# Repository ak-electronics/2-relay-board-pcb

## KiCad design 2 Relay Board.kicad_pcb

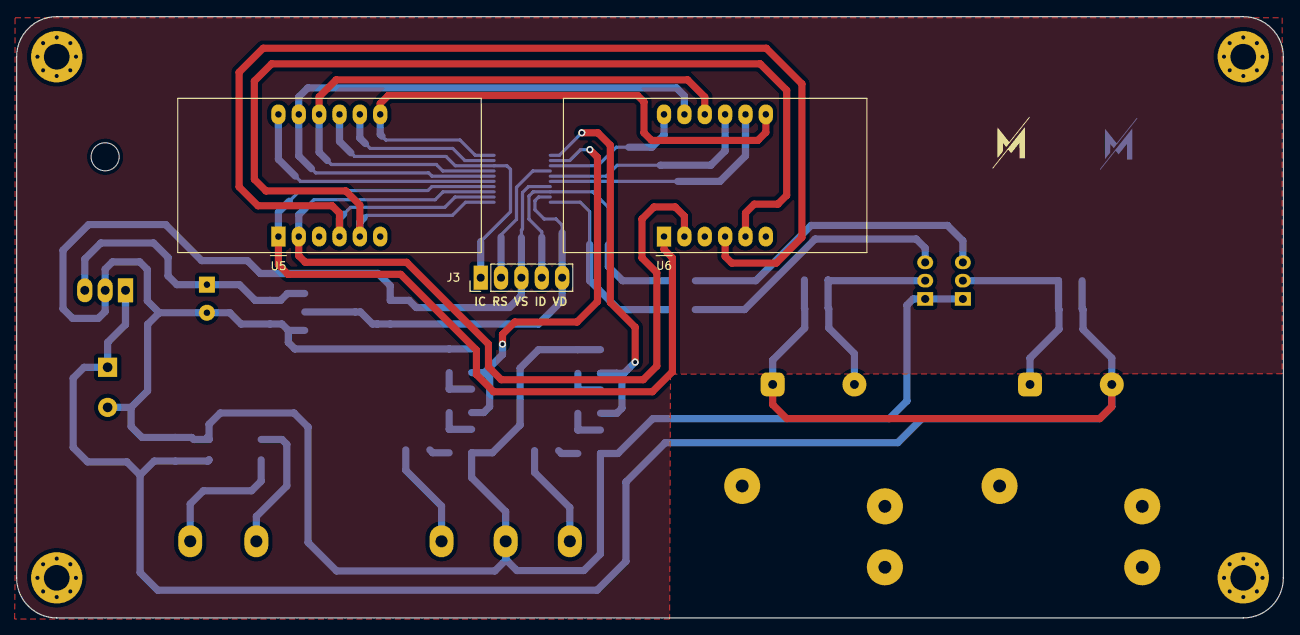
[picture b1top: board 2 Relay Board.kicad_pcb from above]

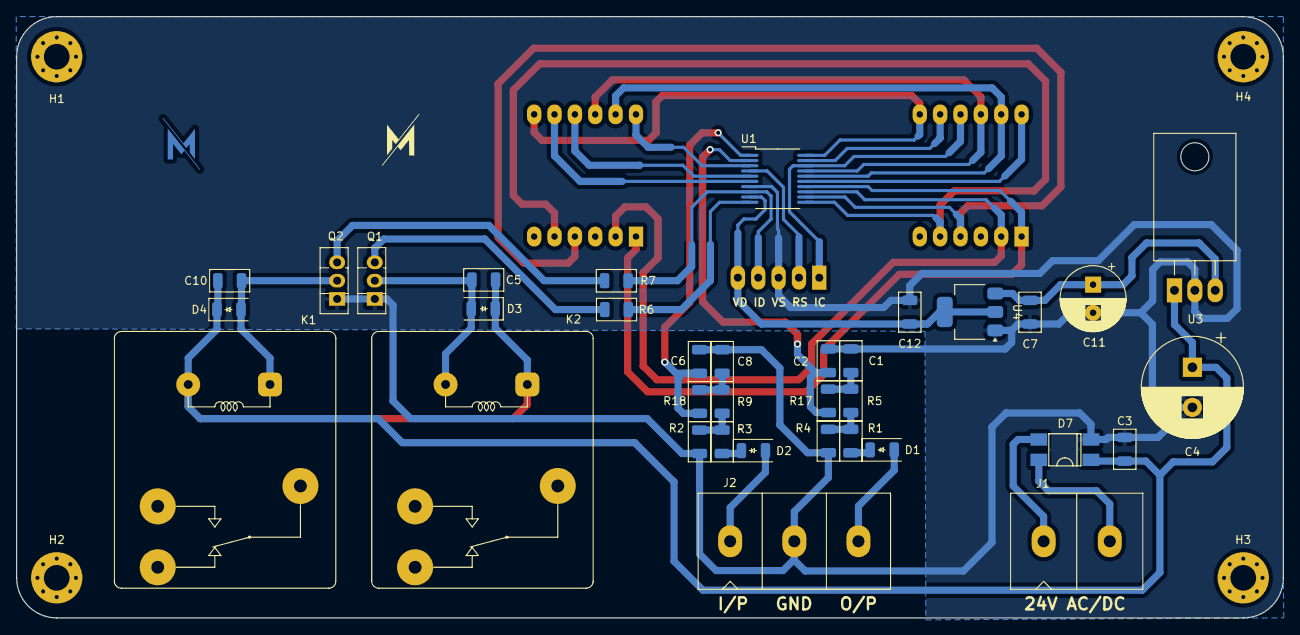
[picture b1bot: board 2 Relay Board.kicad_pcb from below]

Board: 2 copper layers, 158.0 x 75.0 mm, 42 parts (39 on the bottom side), 36 nets.

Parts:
C1, C2, C6, C8, C12: 10uf/50v; C_1206_3216Metric
C3, C5, C7, C10: 0.1uf/50v; C_1206_3216Metric
C4: 1000uf/50v; CP_Radial_D12.5mm_P5.00mm
C11: 470uf/25v; CP_Radial_D8.0mm_P3.50mm
D1, D2, D3, D4: D; D_1206
D7: D_Bridge_+-AA; MB10_bridge
H1, H2, H3, H4: MountingHole; MountingHole_3.2mm_M3_Pad_Via
J1: Conn_01x02; Block_connector_2x1_H1.5_P8
J2: Conn_01x03; Block_connector
J3: Conn_01x05; 5_Pin_PinHeader_1x05_P2.54mm_Vertical
K1, K2: RAYEX-L90; Relay_SPDT_RAYEX-L90Ss
Q1, Q2: BD139; TO-126-3_Vertical
R1, R3: 330K; R_1206_3216Metric
R2, R4: 1.5K; R_1206_3216Metric
R5, R9, R17, R18: 10K; R_1206_3216Metric
R6, R7: 1K; R_1206_3216Metric
U1: N76E003; SSOP-20_5.3x7.2mm_P0.65mm
U3: LM7809_TO220; TO-220-3_Horizontal_TabDown
U4: AMS1117-5.0; SOT-223-3_TabPin2
U5, U6: CA56-12EWA; 3_Digit_CA56-12EWA

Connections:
+12V: C7.2, C11.1, U3.3 (VO), U4.3 (VI)
+24V: C3.2, C4.1, C5.1, C10.1, D3.1 (K), D4.1 (K), D7.1 (+), K1.A2, K2.A1, U3.1 (VI)
A: U1.16 (P00), U5.11 (a), U6.11 (a)
B: U1.20 (P04), U5.7 (b), U6.7 (b)
C: U1.12 (P13), U5.4 (c), U6.4 (c)
D: U1.13 (P12), U5.2 (d), U6.2 (d)
DG1: U1.15 (P10), U5.12 (CA1)
DG2: J3.1, U1.18 (P02/SWIM), U5.9 (CA2)
DG3: U1.19 (P03), U5.8 (CA3)
DG4: U1.3 (P07), U6.12 (CA1)
DG5: U1.5 (P30), U6.9 (CA2)
DG6: U1.6 (P17), U6.8 (CA3)
E: U1.14 (P11), U5.1 (e), U6.1 (e)
F: U1.17 (P01), U5.10 (f), U6.10 (f)
G: U1.11 (P14), U5.5 (g), U6.5 (g)
I-P_voltage: C6.1, R18.1, U1.1 (P05)
INPUT_volt: D2.2 (A), J2.1
unnamed: C1.1, R5.1, R17.2
unnamed: C8.1, R9.1, R18.2
unnamed: D1.1 (K), R1.1
unnamed: D2.1 (K), R3.1
unnamed: C5.2, D3.2 (A), K2.A2, Q1.2 (C)
unnamed: C10.2, D4.2 (A), K1.A1, Q2.2 (C)
unnamed: D7.4, J1.1
unnamed: D7.3, J1.2
unnamed: Q1.3 (B), R6.1
unnamed: Q2.3 (B), R7.1
unnamed: R1.2, R4.1, R5.2
unnamed: R2.1, R3.2, R9.2
O-P_voltage: C2.1, R17.1, U1.2 (P06)
OUTPUT_volt: D1.2 (A), J2.3
RST: J3.2, U1.4 (P20/RST)
Relay 1: J3.4, R7.2, U1.8 (P16/VCAP)
Relay 2: R6.2, U1.10 (P15)
VDD: C12.2, J3.5, U1.9 (VDD), U4.2 (VO)
VSS: C1.2, C2.2, C3.1, C4.2, C6.2, C7.1, C8.2, C11.2, C12.1, D7.2 (-), J2.2, J3.3, Q1.1 (E), Q2.1 (E), R2.2, R4.2, U1.7 (GND), U3.2 (GND), U4.1 (GND)

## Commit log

2024-12-08 first commit v1.0
2024-12-08 this version hase small 7805 v1.1
2024-12-08 this version hase smd LDO v1.2
